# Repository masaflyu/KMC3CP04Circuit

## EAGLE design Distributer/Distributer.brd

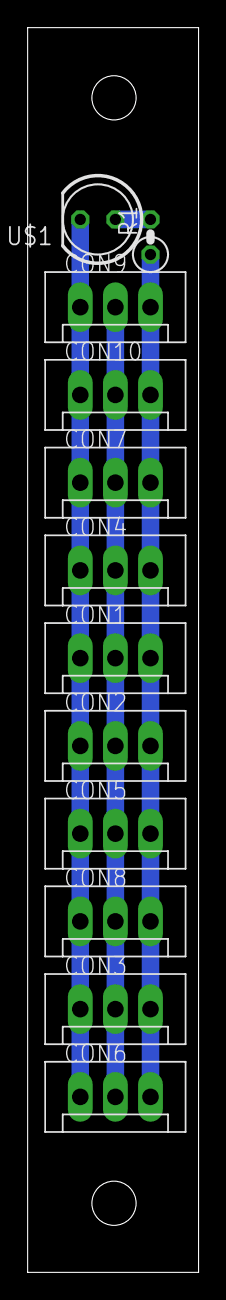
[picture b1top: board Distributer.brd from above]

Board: 2 copper layers, 12.4 x 90.1 mm, 12 parts (0 on the bottom side), 4 nets.

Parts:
CON1, CON2, CON3, CON4, CON5, CON6, CON7, CON8, CON9, CON10: CON3
R1: 2k; 1/4W-V1_(0207/2V)
U$1: LED(砲弾型)5; LED5MM

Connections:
GND: CON1.P$3, CON2.P$3, CON3.P$3, CON4.P$3, CON5.P$3, CON6.P$3, CON7.P$3, CON8.P$3, CON9.P$3, CON10.P$3, U$1.K
unnamed: CON1.P$1, CON2.P$1, CON3.P$1, CON4.P$1, CON5.P$1, CON6.P$1, CON7.P$1, CON8.P$1, CON9.P$1, CON10.P$1, R1.1
unnamed: CON1.P$2, CON2.P$2, CON3.P$2, CON4.P$2, CON5.P$2, CON6.P$2, CON7.P$2, CON8.P$2, CON9.P$2, CON10.P$2
unnamed: R1.2, U$1.A

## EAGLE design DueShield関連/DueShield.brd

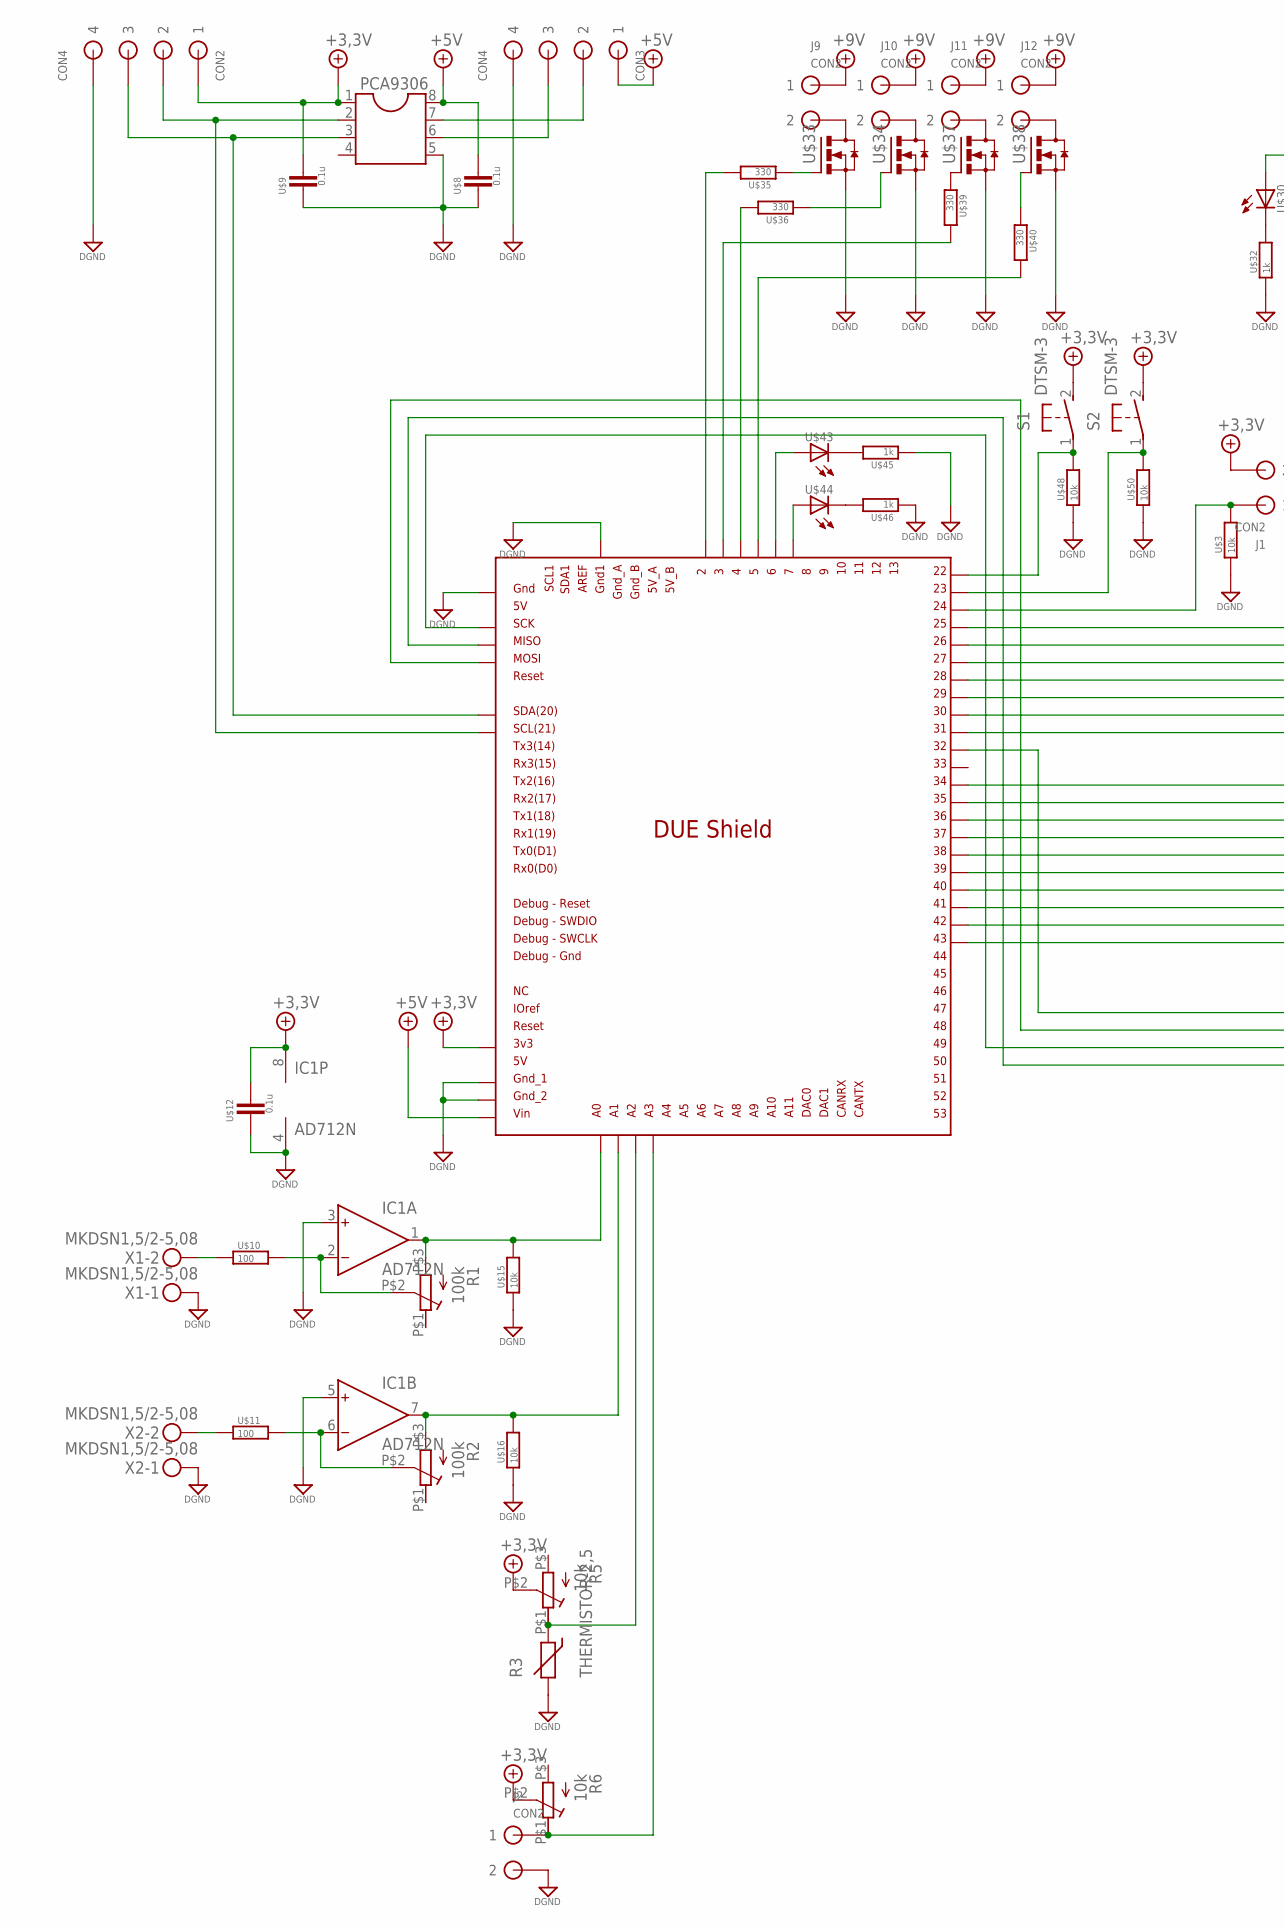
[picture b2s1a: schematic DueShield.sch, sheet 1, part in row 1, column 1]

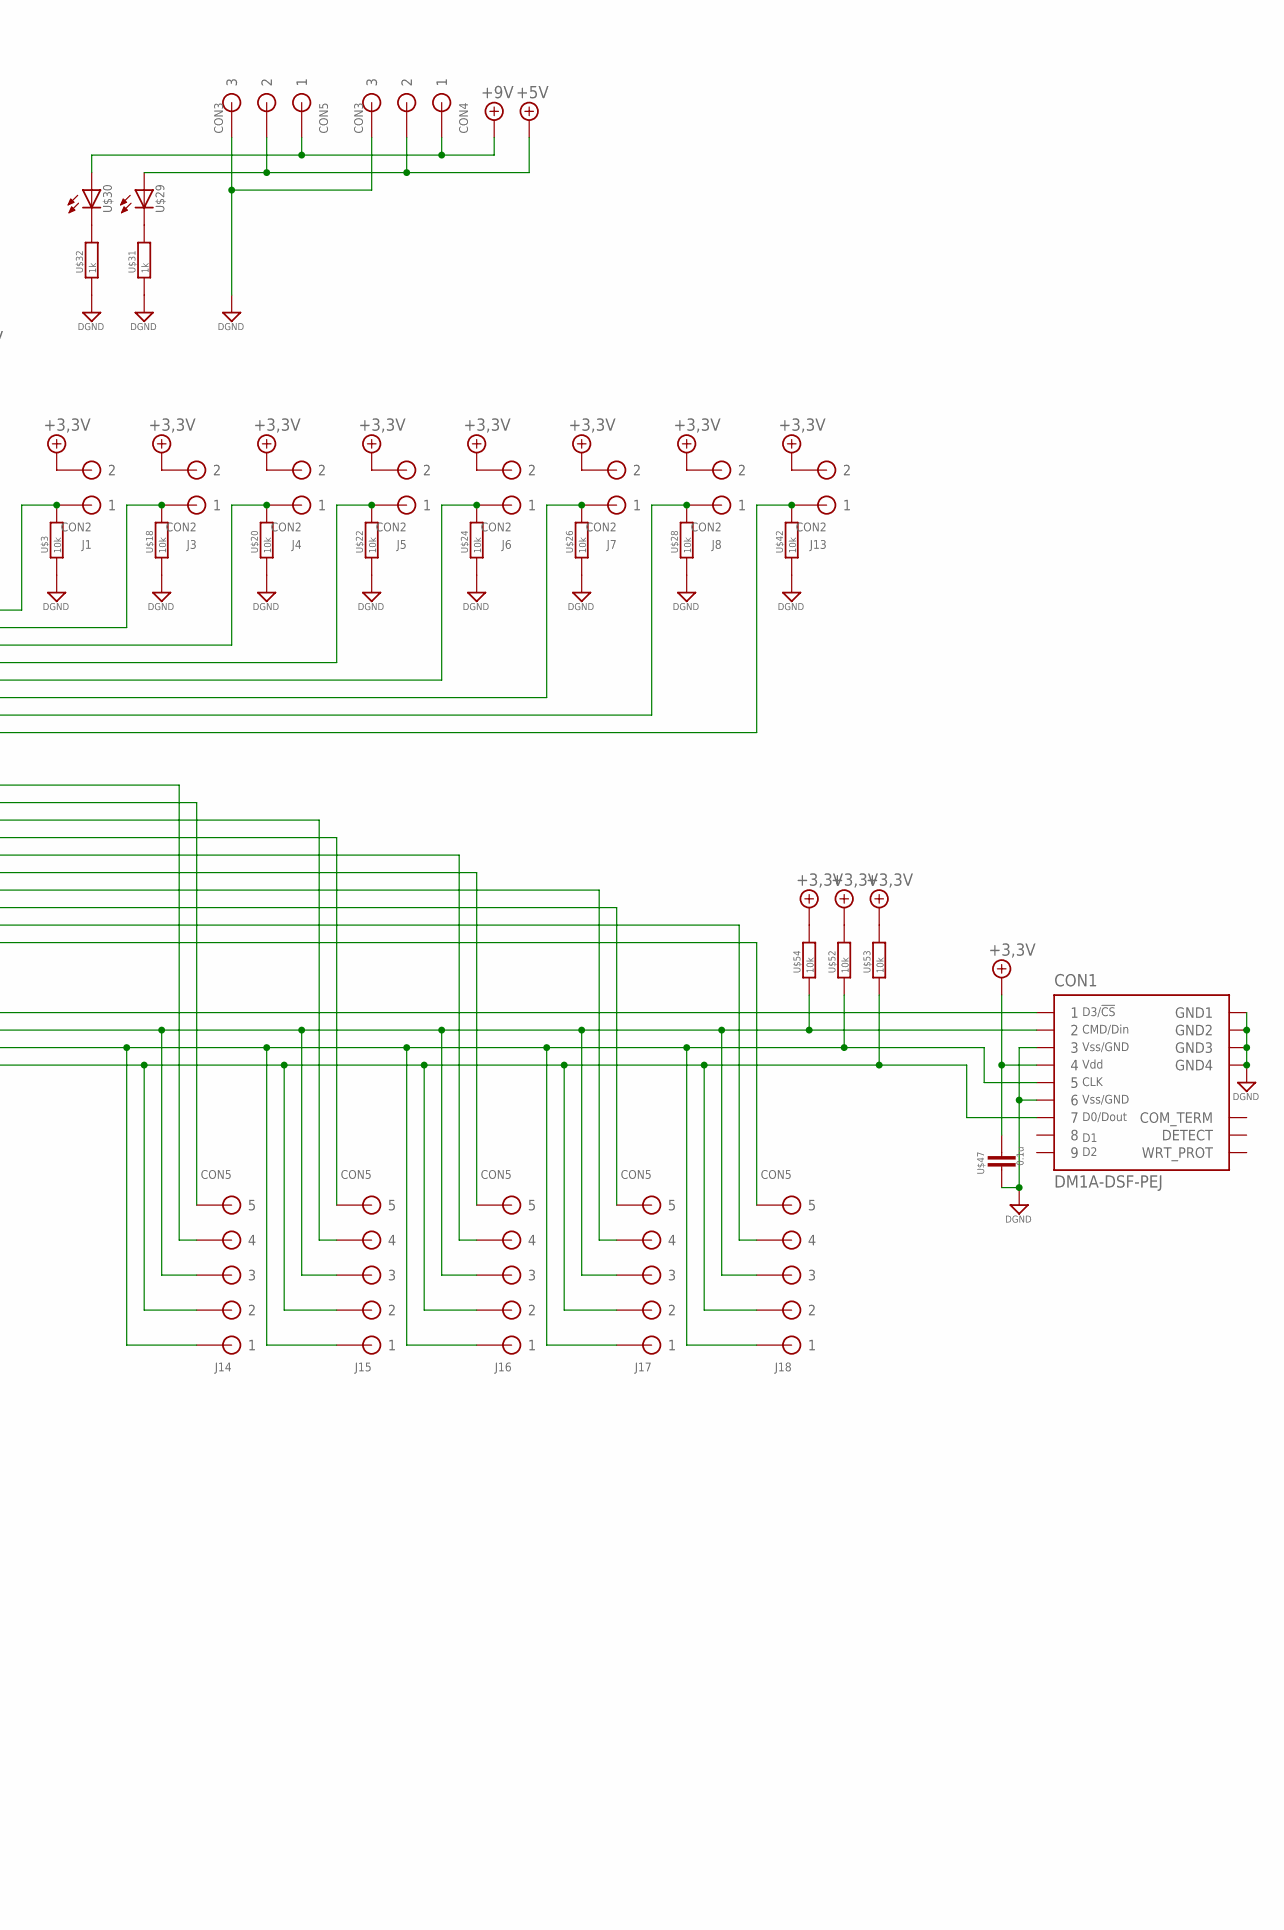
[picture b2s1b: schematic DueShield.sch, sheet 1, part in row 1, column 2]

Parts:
CON1: DM1A-DSF-PEJ
CON2, CON3: CON4
CON4, CON5: CON3
IC1: AD712N; DIL08
J1, J2, J3, J4, J5, J6, J7, J8, J9, J10, J11, J12, J13: CON2
J14, J15, J16, J17, J18: CON5
PCA9306: DIL8; DIL08
R1, R2: 100k; GF063PB
R3: THERMISTOR-2,5; RS-2,5
R5, R6: 10k; GF063PB
S1, S2: DTSM-3
U$1: DUE(3DPRINTER); DUE(3DPRITNER)
U$3, U$15, U$16, U$18, U$20, U$22, U$24, U$26, U$28, U$42, U$48, U$50, U$52, U$53, U$54: 10k; 0805
U$8, U$9, U$12, U$47: 0.1u; 0805
U$10, U$11: 100; 0805
U$29, U$30, U$43, U$44: LED(砲弾型)3; LED3MM
U$31, U$32, U$45, U$46: 1k; 0805
U$33, U$34, U$37, U$38: TO-252(MOS-FET_N); TO-252
U$35, U$36, U$39, U$40: 330; 0805
X1, X2: MKDSN1,5/2-5,08

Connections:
+3.3V: CON1.4, CON2.P$1 (1), IC1.8 (V+), J1.P$2 (2), J3.P$2 (2), J4.P$2 (2), J5.P$2 (2), J6.P$2 (2), J7.P$2 (2), J8.P$2 (2), J13.P$2 (2), PCA9306.1, R5.P$2 (S), R6.P$2 (S), S1.2, S2.2, U$1.3V3, U$9.1, U$12.1, U$47.1, U$52.2, U$53.2, U$54.2
+5V: CON3.P$1 (1), CON4.P$2 (2), CON5.P$2 (2), PCA9306.8, U$1.VIN, U$8.1, U$29.A
+5V1: U$1.6, U$43.A
+9V: CON4.P$1 (1), CON5.P$1 (1), J9.P$1 (1), J10.P$1 (1), J11.P$1 (1), J12.P$1 (1), U$30.A
+9V1: U$1.7, U$44.A
DGND: CON1.3, CON1.6, CON1.GND1, CON1.GND2, CON1.GND3, CON1.GND4, CON2.P$4 (4), CON3.P$4 (4), CON4.P$3 (3), CON5.P$3 (3), IC1.3 (IN+), IC1.4 (V-), IC1.5 (IN+), J2.P$2 (2), PCA9306.5, R3.2, U$1.5V_ICSP, U$1.GND1, U$1.GND_1, U$1.GND_2, U$3.1, U$8.2, U$9.2, U$12.2, U$15.1, U$16.1, U$18.1, U$20.1, U$22.1, U$24.1, U$26.1, U$28.1, U$31.1, U$32.1, U$33.2 (S), U$34.2 (S), U$37.2 (S), U$38.2 (S), U$42.1, U$45.1, U$46.1, U$47.2, U$48.1, U$50.1, X1.1, X2.1
unnamed: J1.P$1 (1), U$1.24, U$3.2
unnamed: CON1.7, J14.P$2 (2), J15.P$2 (2), J16.P$2 (2), J17.P$2 (2), J18.P$2 (2), U$1.MISO_ICSP, U$53.1
unnamed: S1.1, U$1.22, U$48.2
unnamed: CON1.1, U$1.32
unnamed: CON2.P$2 (2), PCA9306.2, U$1.SCL
unnamed: CON1.5, J14.P$1 (1), J15.P$1 (1), J16.P$1 (1), J17.P$1 (1), J18.P$1 (1), U$1.SCK_ICSP, U$52.1
unnamed: CON2.P$3 (3), PCA9306.3, U$1.SDA
unnamed: CON3.P$2 (2), PCA9306.7
unnamed: CON3.P$3 (3), PCA9306.6
unnamed: IC1.2 (IN-), R1.P$2 (S), U$10.2
unnamed: IC1.6 (IN-), R2.P$2 (S), U$11.2
unnamed: J13.P$1 (1), U$1.31, U$42.2
unnamed: U$11.1, X2.2
unnamed: U$10.1, X1.2
unnamed: J2.P$1 (1), R6.P$1 (E), U$1.A3
unnamed: J3.P$1 (1), U$1.25, U$18.2
unnamed: IC1.1 (OUT), R1.P$3 (A), U$1.A0, U$15.2
unnamed: IC1.7 (OUT), R2.P$3 (A), U$1.A1, U$16.2
unnamed: R3.1, R5.P$1 (E), U$1.A2
unnamed: J4.P$1 (1), U$1.26, U$20.2
unnamed: J5.P$1 (1), U$1.27, U$22.2
unnamed: J6.P$1 (1), U$1.28, U$24.2
unnamed: J7.P$1 (1), U$1.29, U$26.2
unnamed: J8.P$1 (1), U$1.30, U$28.2
unnamed: U$1.2, U$35.2
unnamed: U$1.4, U$36.2
unnamed: U$1.3, U$39.2
unnamed: U$1.5, U$40.2
unnamed: U$29.K, U$31.2
unnamed: U$30.K, U$32.2
unnamed: U$43.K, U$45.2
unnamed: U$33.1 (G), U$35.1
unnamed: U$34.1 (G), U$36.1
unnamed: J9.P$2 (2), U$33.3 (D)
unnamed: J10.P$2 (2), U$34.3 (D)
unnamed: U$37.1 (G), U$39.1
unnamed: U$38.1 (G), U$40.1
unnamed: J11.P$2 (2), U$37.3 (D)
unnamed: J12.P$2 (2), U$38.3 (D)
unnamed: U$44.K, U$46.2
unnamed: J14.P$4 (4), U$1.34
unnamed: J14.P$5 (5), U$1.35
unnamed: CON1.2, J14.P$3 (3), J15.P$3 (3), J16.P$3 (3), J17.P$3 (3), J18.P$3 (3), U$1.MOSI_ICSP, U$54.1
unnamed: S2.1, U$1.23, U$50.2
unnamed: J15.P$5 (5), U$1.37
unnamed: J15.P$4 (4), U$1.36
unnamed: J16.P$4 (4), U$1.38
unnamed: J16.P$5 (5), U$1.39
unnamed: J17.P$4 (4), U$1.40
unnamed: J17.P$5 (5), U$1.41
unnamed: J18.P$4 (4), U$1.42
unnamed: J18.P$5 (5), U$1.43

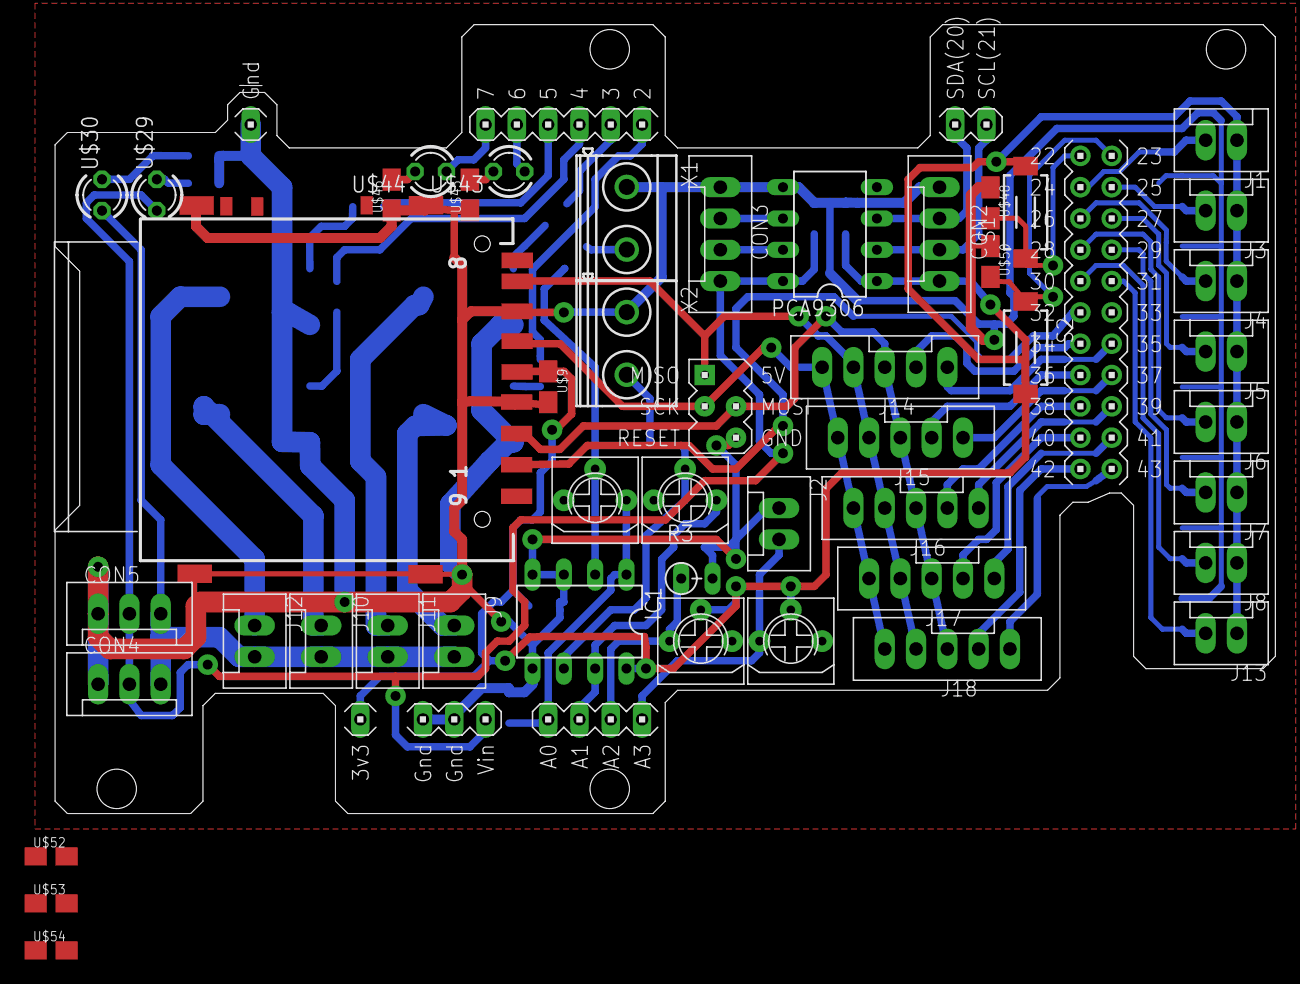
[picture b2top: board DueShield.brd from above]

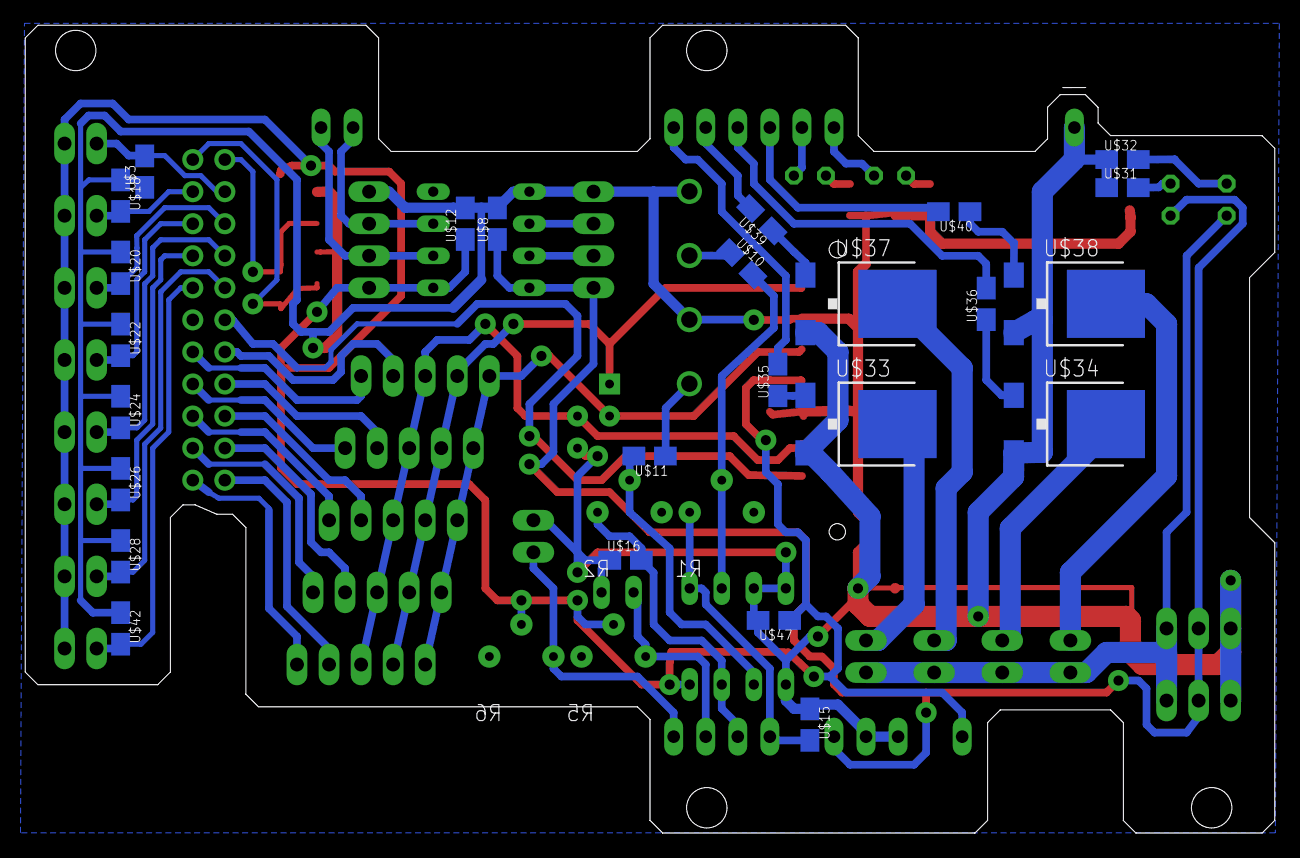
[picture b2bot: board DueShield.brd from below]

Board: 2 copper layers, 99.0 x 64.0 mm, 72 parts (25 on the bottom side), 58 nets.

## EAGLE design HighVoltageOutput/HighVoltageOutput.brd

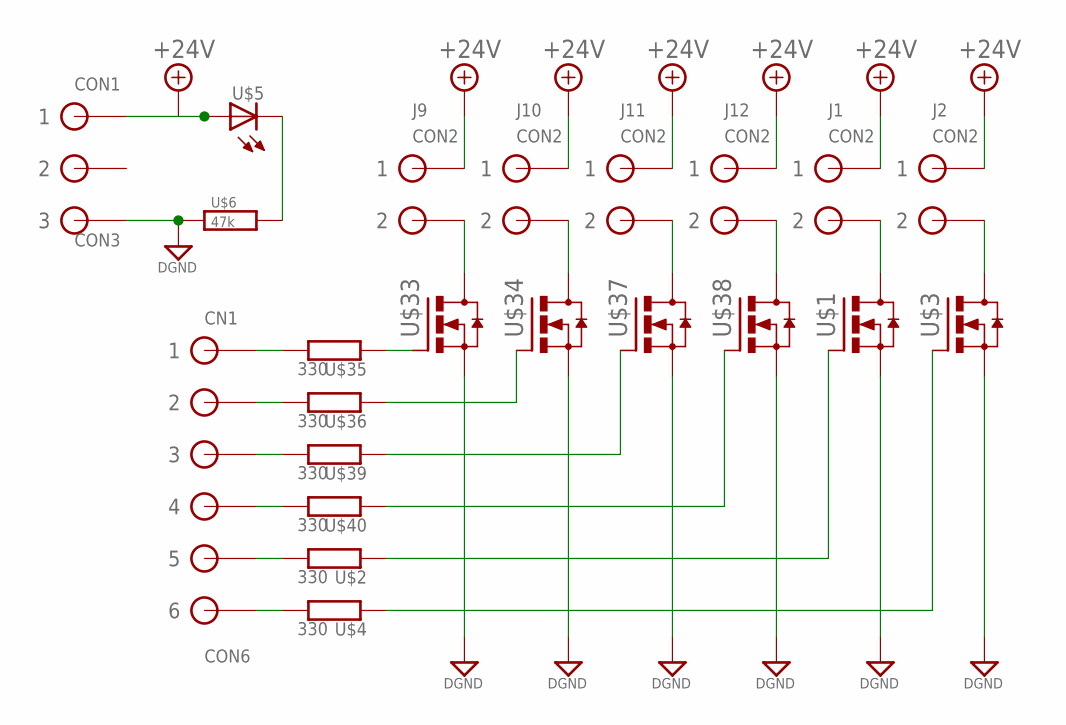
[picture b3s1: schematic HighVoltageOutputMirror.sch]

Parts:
CN1: CON6
CON1: CON3
J1, J2, J9, J10, J11, J12: CON2
U$1, U$3, U$33, U$34, U$37, U$38: TO-252(MOS-FET_N)TO-252FORHAND; TO-252FORHAND
U$2, U$4, U$35, U$36, U$39, U$40: 330; 1/4W-H4_(0207/10)
U$5: LED(砲弾型)3; LED3MM
U$6: 47k; 0805(JIS2012)HAND

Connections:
+24V: CON1.P$1 (1), J1.P$1 (1), J2.P$1 (1), J9.P$1 (1), J10.P$1 (1), J11.P$1 (1), J12.P$1 (1), U$5.A
DGND: CON1.P$3 (3), U$1.2 (S), U$3.2 (S), U$6.1, U$33.2 (S), U$34.2 (S), U$37.2 (S), U$38.2 (S)
unnamed: CN1.P$5 (5), U$2.2
unnamed: U$1.1 (G), U$2.1
unnamed: J1.P$2 (2), U$1.3 (D)
unnamed: CN1.P$6 (6), U$4.2
unnamed: U$3.1 (G), U$4.1
unnamed: J2.P$2 (2), U$3.3 (D)
unnamed: CN1.P$2 (2), U$36.2
unnamed: U$5.K, U$6.2
unnamed: CN1.P$1 (1), U$35.2
unnamed: CN1.P$3 (3), U$39.2
unnamed: CN1.P$4 (4), U$40.2
unnamed: U$33.1 (G), U$35.1
unnamed: U$34.1 (G), U$36.1
unnamed: J9.P$2 (2), U$33.3 (D)
unnamed: J10.P$2 (2), U$34.3 (D)
unnamed: U$37.1 (G), U$39.1
unnamed: U$38.1 (G), U$40.1
unnamed: J11.P$2 (2), U$37.3 (D)
unnamed: J12.P$2 (2), U$38.3 (D)

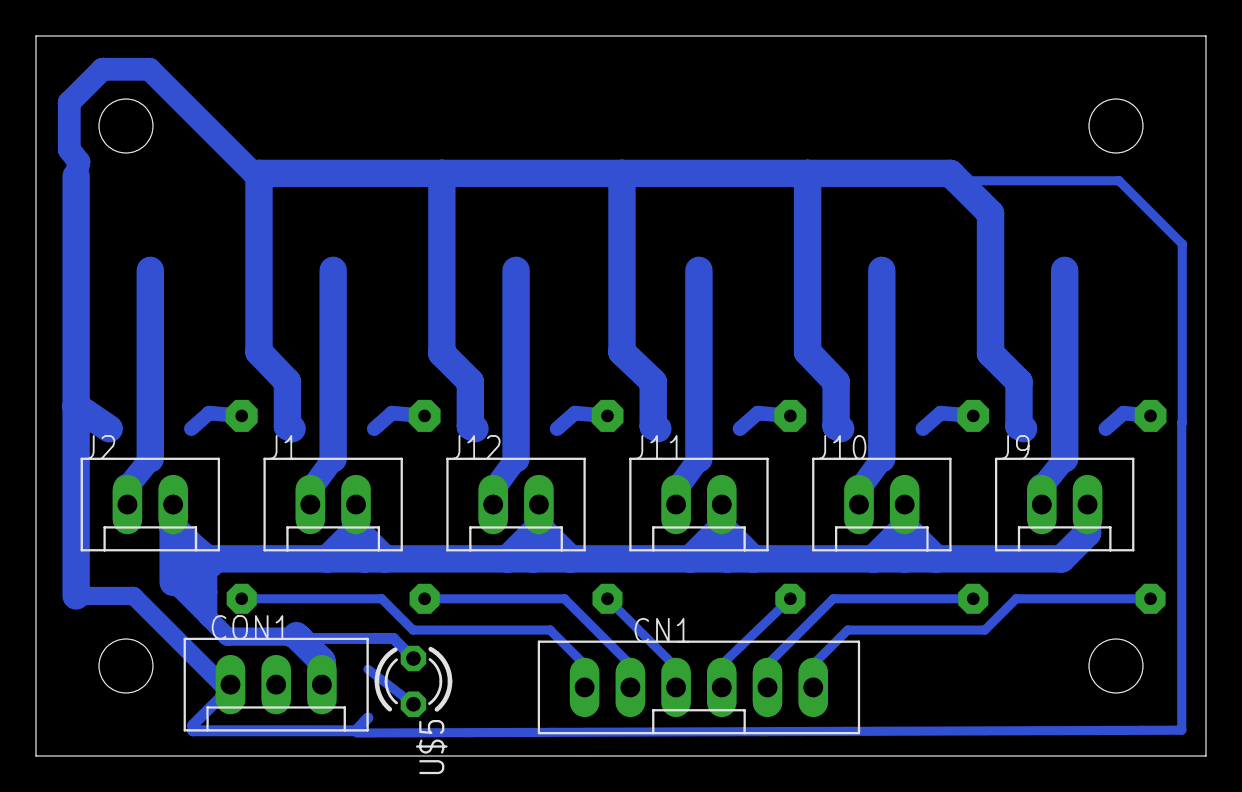
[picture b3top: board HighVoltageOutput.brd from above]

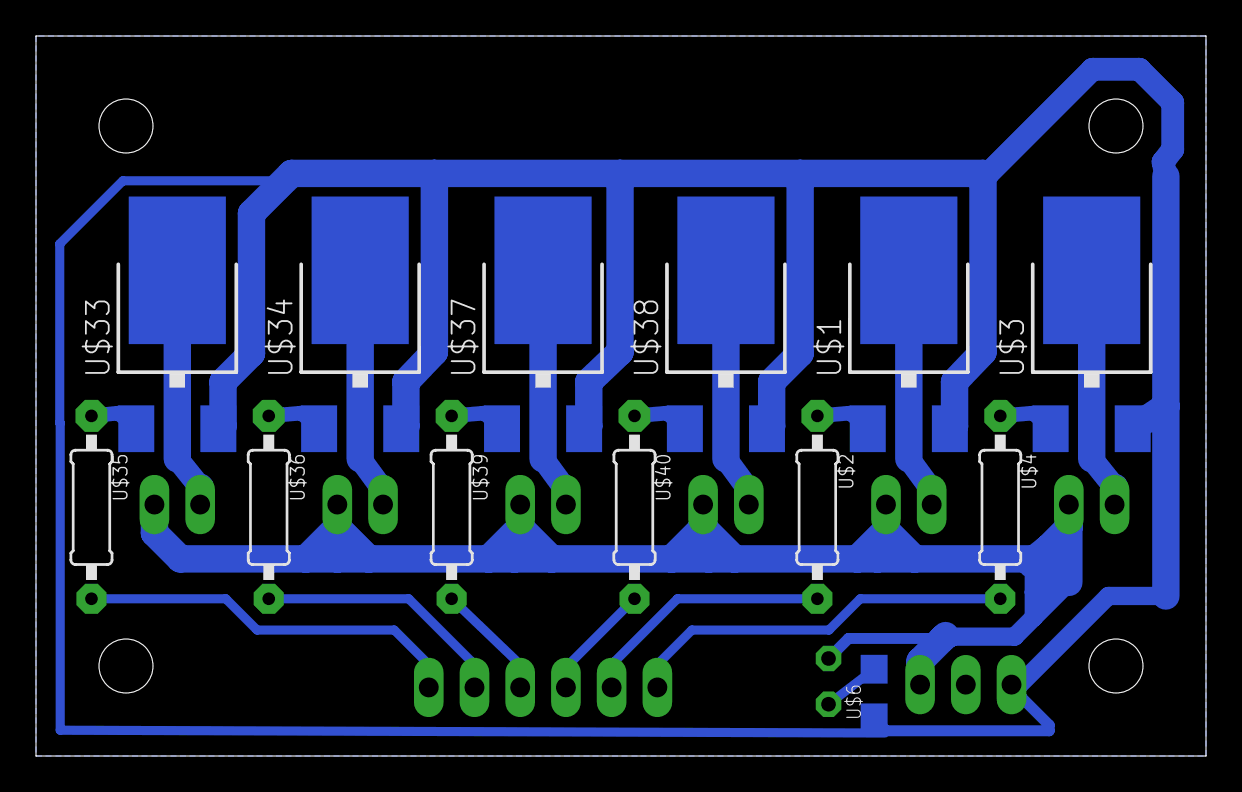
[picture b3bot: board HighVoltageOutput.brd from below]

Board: 2 copper layers, 65.0 x 40.0 mm, 22 parts (13 on the bottom side), 21 nets.

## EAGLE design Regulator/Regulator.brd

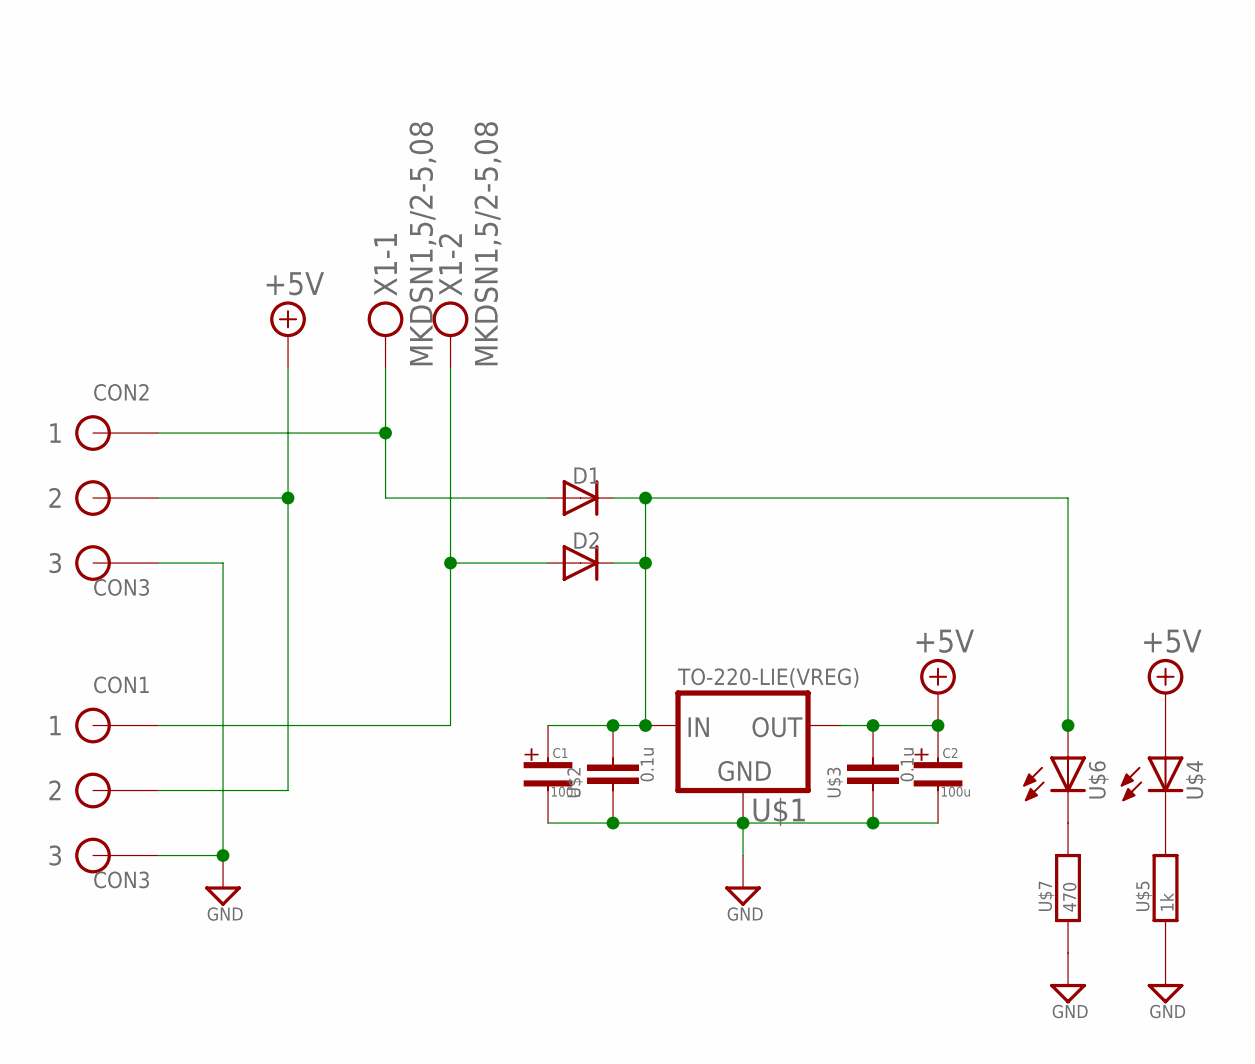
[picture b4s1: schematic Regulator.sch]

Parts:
C1, C2: 100u; D=1,φ=5
CON1, CON2: CON3
D1, D2: (汎用)D=3; DO41(D=3)
U$1: TO-220-LIE(VREG); TO-220(LIE)
U$2, U$3: 0.1u; 0805
U$4, U$6: LED(砲弾型)3; LED3MM
U$5: 1k; 0805
U$7: 470; 0805
X1: MKDSN1,5/2-5,08

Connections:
+5V: C2.+, CON1.P$2 (2), CON2.P$2 (2), U$1.3 (OUT), U$3.1, U$4.A
+9V: C1.+, D1.C, D2.C, U$1.1 (IN), U$2.1, U$6.A
GND: C1.-, C2.-, CON1.P$3 (3), CON2.P$3 (3), U$1.2 (GND), U$2.2, U$3.2, U$5.1, U$7.1
unnamed: CON2.P$1 (1), D1.A, X1.1
unnamed: CON1.P$1 (1), D2.A, X1.2
unnamed: U$4.K, U$5.2
unnamed: U$6.K, U$7.2

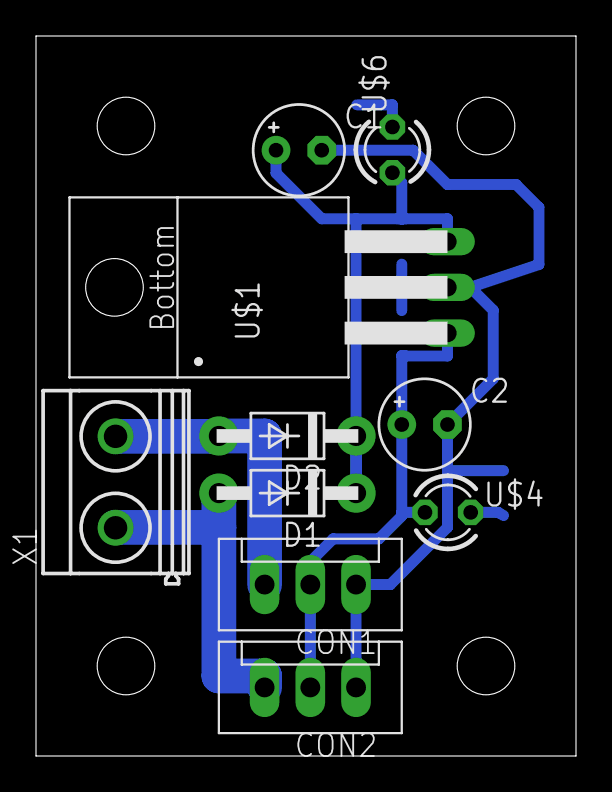
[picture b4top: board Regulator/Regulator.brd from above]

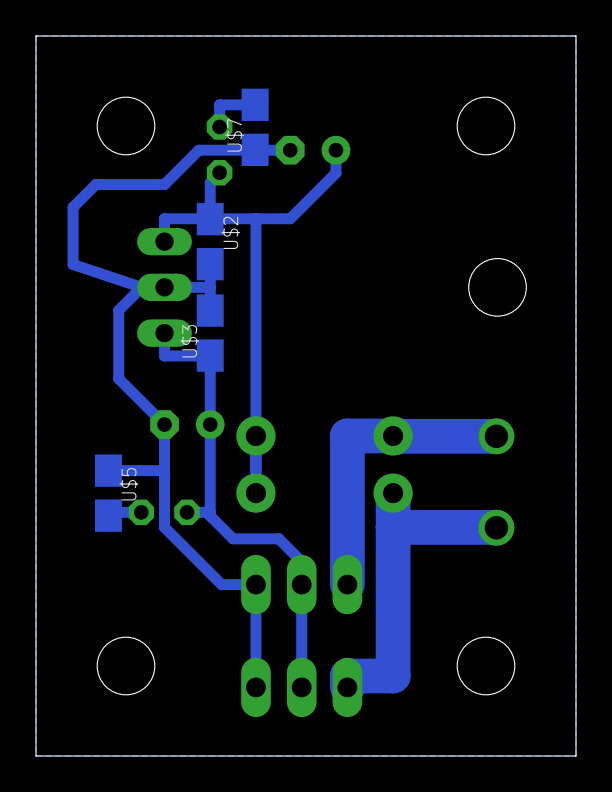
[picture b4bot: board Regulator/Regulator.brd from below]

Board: 2 copper layers, 30.0 x 40.0 mm, 14 parts (4 on the bottom side), 7 nets.

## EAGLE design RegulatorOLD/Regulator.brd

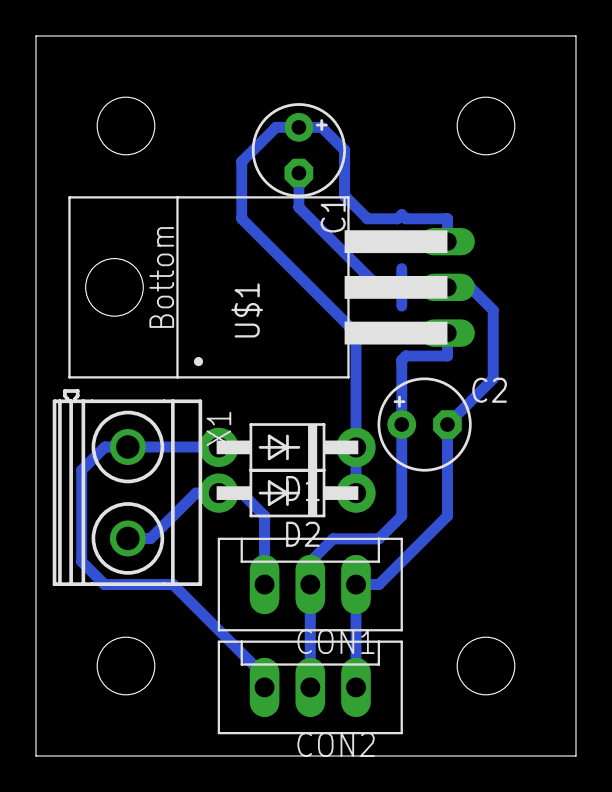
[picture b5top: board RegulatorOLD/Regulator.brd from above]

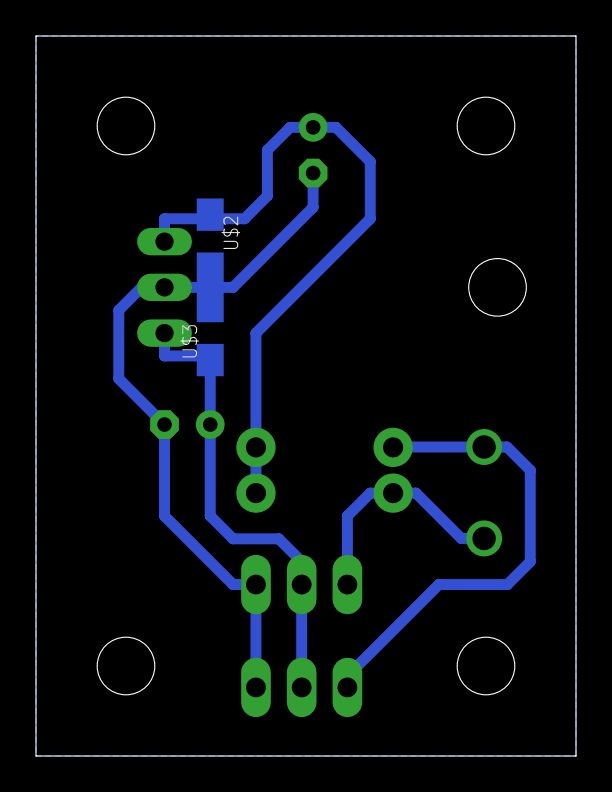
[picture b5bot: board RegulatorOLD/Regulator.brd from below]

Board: 2 copper layers, 30.0 x 40.0 mm, 10 parts (2 on the bottom side), 5 nets.

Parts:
C1, C2: 100u; D=1,φ=5
CON1, CON2: CON3
D1, D2: (汎用)D=3; DO41(D=3)
U$1: TO-220-LIE(VREG); TO-220(LIE)
U$2, U$3: 0.1u; 0805
X1: MKDSN1,5/2-5,08

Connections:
+5V: C2.+, CON1.P$2, CON2.P$2, U$1.3, U$3.1
GND: C1.-, C2.-, CON1.P$3, CON2.P$3, U$1.2, U$2.2, U$3.2
unnamed: CON2.P$1, D1.A, X1.1
unnamed: CON1.P$1, D2.A, X1.2
unnamed: C1.+, D1.C, D2.C, U$1.1, U$2.1

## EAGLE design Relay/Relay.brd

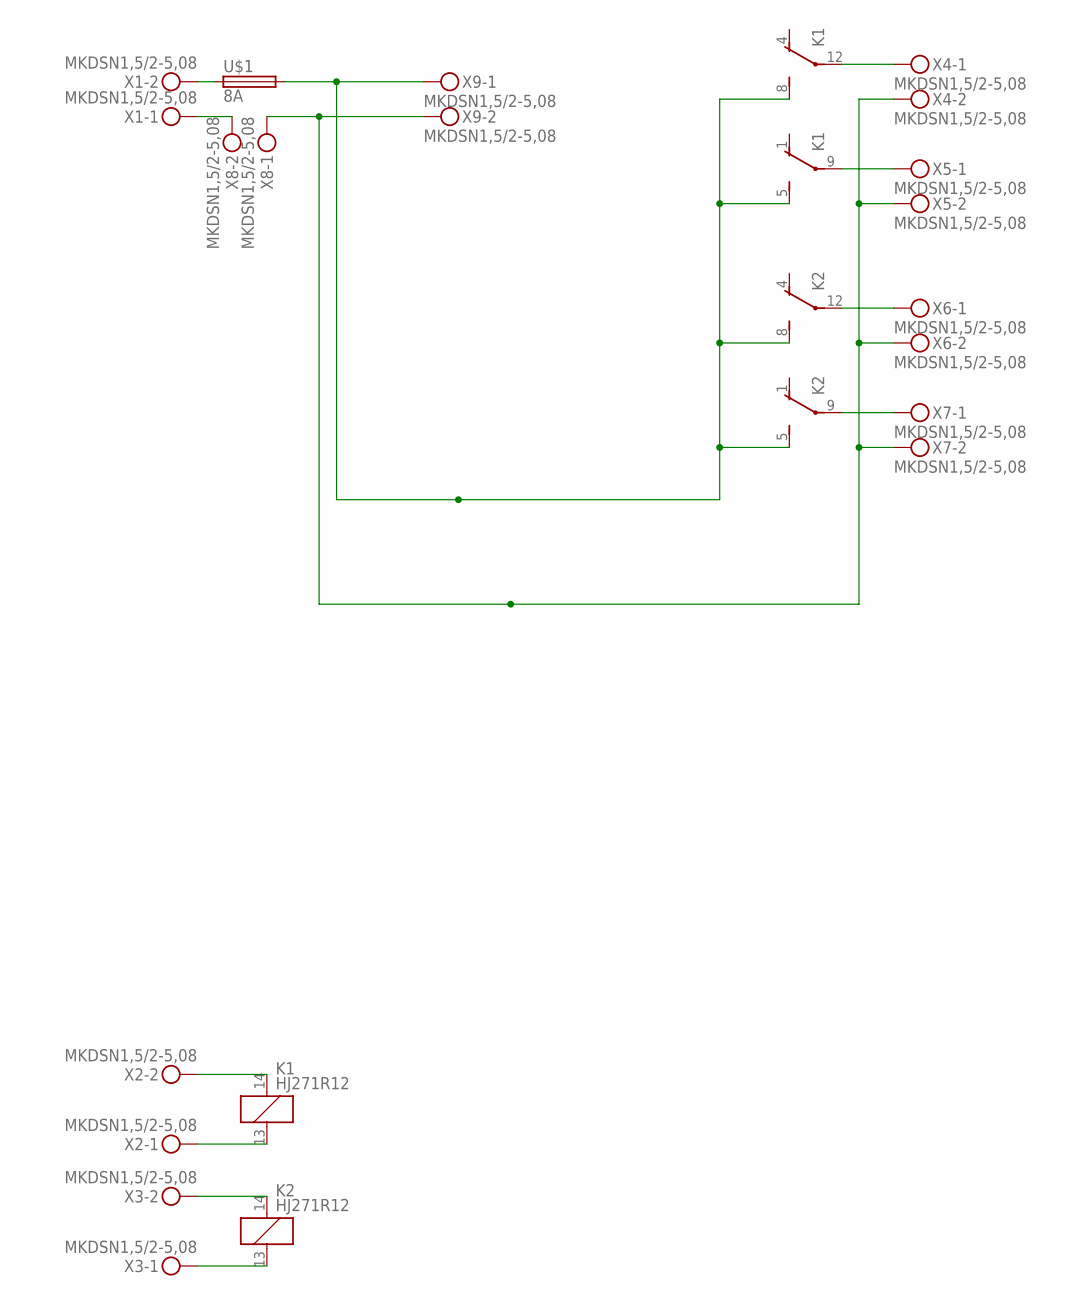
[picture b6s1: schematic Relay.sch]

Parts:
K1, K2: HJ271R12; PT-2
U$1: 8A; MF550
X1, X2, X3, X4, X5, X6, X7, X8, X9: MKDSN1,5/2-5,08

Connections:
unnamed: K1.12, X4.1
unnamed: K1.9, X5.1
unnamed: K2.12, X6.1
unnamed: K2.9, X7.1
unnamed: K1.14 (1), X2.2
unnamed: K1.13 (2), X2.1
unnamed: K2.14 (1), X3.2
unnamed: K2.13 (2), X3.1
unnamed: X1.1, X8.2
unnamed: K1.5 (S), K1.8 (S), K2.5 (S), K2.8 (S), U$1.P$2 (2), X9.1
unnamed: U$1.P$1 (1), X1.2
unnamed: X4.2, X5.2, X6.2, X7.2, X8.1, X9.2

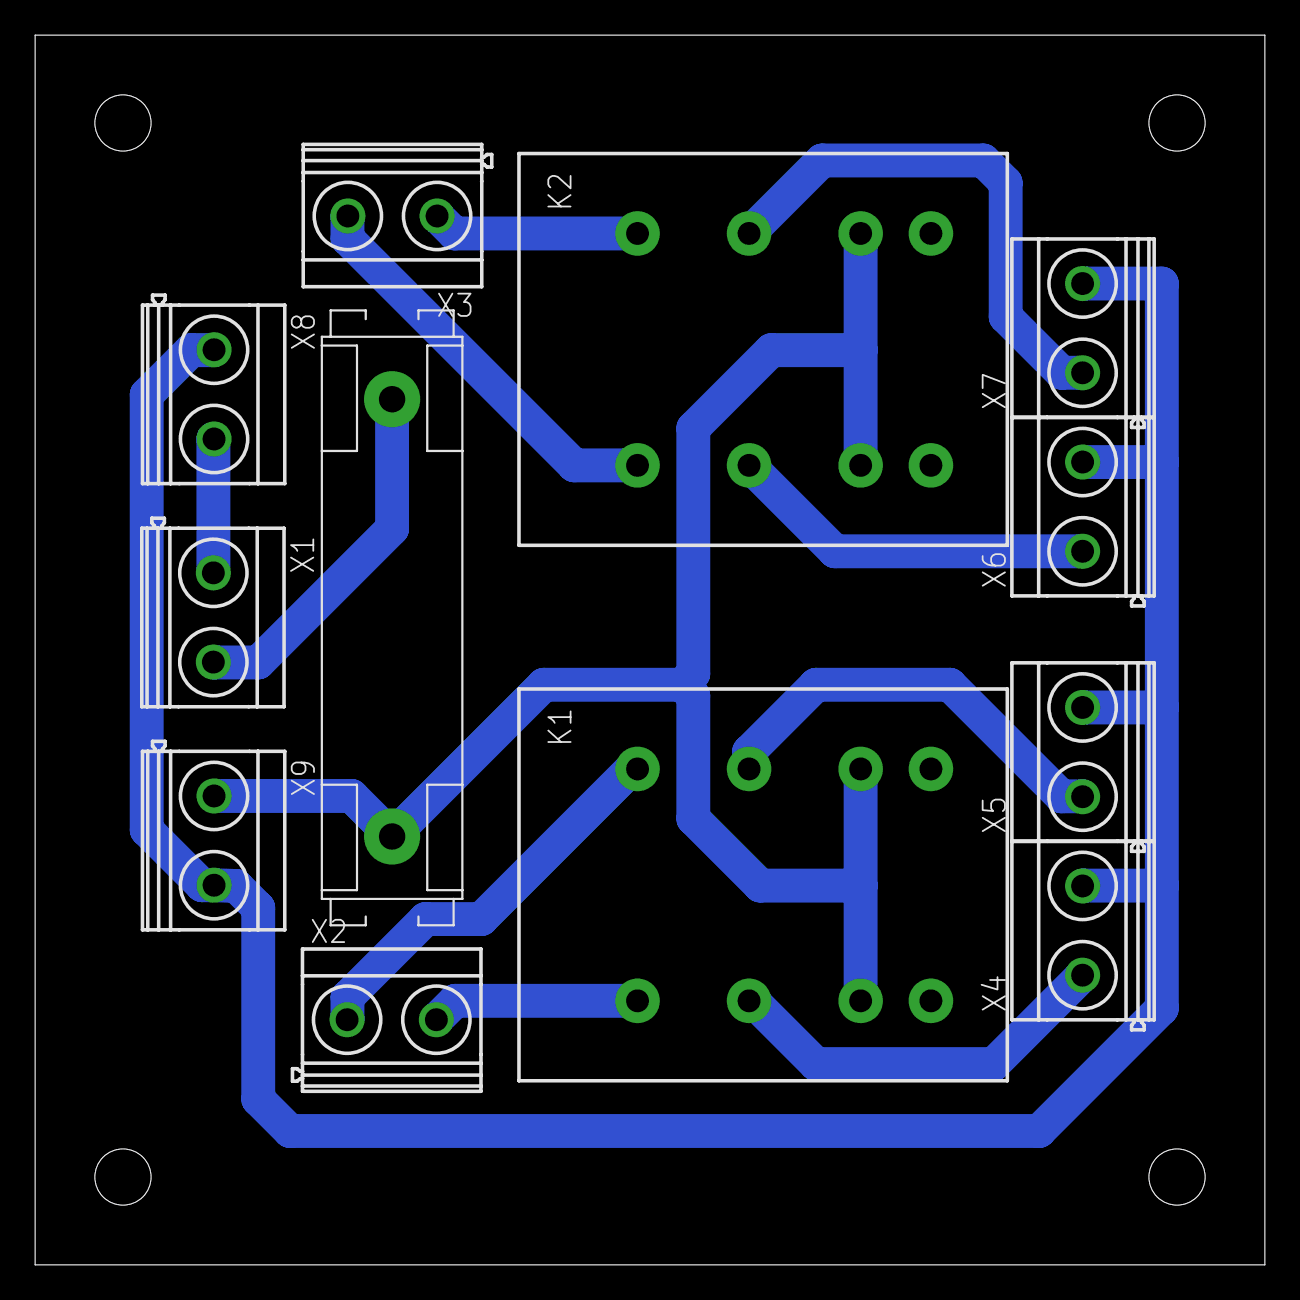
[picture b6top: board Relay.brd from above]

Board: 2 copper layers, 70.0 x 70.0 mm, 12 parts (0 on the bottom side), 12 nets.
